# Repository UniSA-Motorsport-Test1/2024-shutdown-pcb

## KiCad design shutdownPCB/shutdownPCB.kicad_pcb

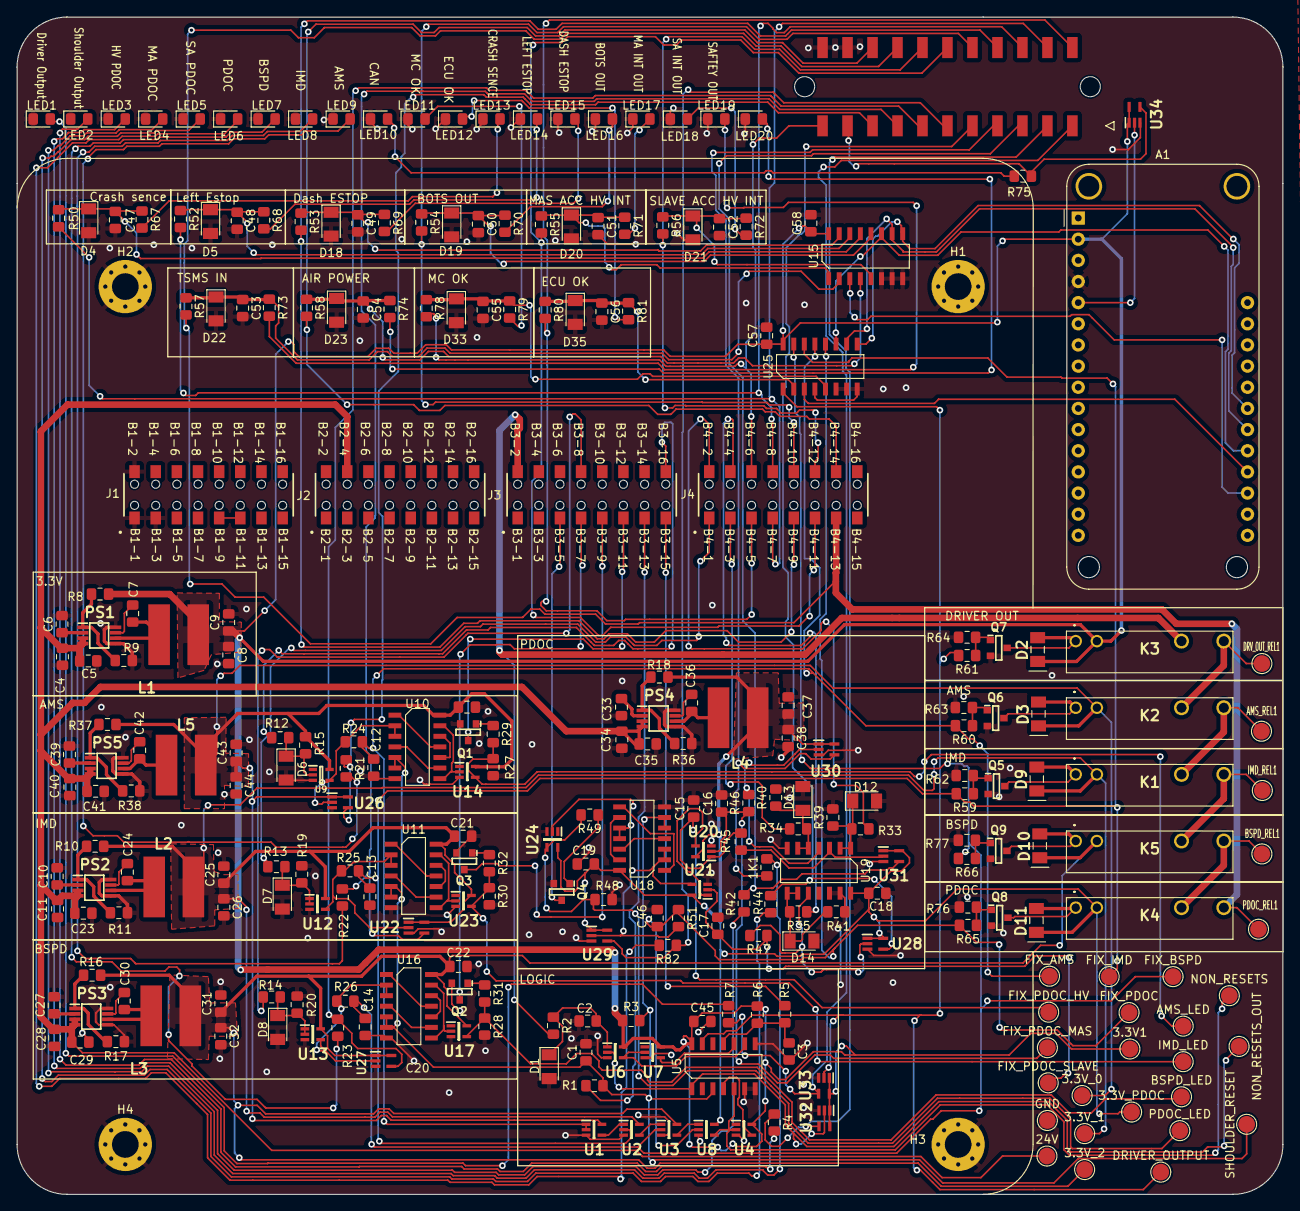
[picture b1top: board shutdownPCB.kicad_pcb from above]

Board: 2 copper layers, 152.0 x 141.4 mm, 277 parts (0 on the bottom side), 168 nets.

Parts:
1K1: CRCW0805; 0805
3.3V1, 3.3V_0, 3.3V_1, 3.3V_2, 3.3V_PDOC, 24V: TestPoint; TestPoint_Pad_D2.0mm
A1: Adafruit_Feather_Generic; Adafruit_Feather_WithMountingHoles
AMS_LED: TestPoint; TestPoint_Pad_D2.0mm
AMS_REL1: TestPoint; TestPoint_Pad_D2.0mm
BSPD_LED: TestPoint; TestPoint_Pad_D2.0mm
BSPD_REL1: TestPoint; TestPoint_Pad_D2.0mm
C1, C2, C3, C12, C13, C14, C15, C16, C17, C46, C47, C48, C49, C50, C51, C52, C53, C54, C55, C56: GCM0805_1u; 0805
C4, C5, C8, C9, C11, C23, C25, C26, C28, C29, C31, C32, C34, C35, C37, C38, C40, C41, C43, C44: 10uF; 0805
C6, C10, C27, C33, C39: 1uF; 0805
C7, C24, C30, C36, C42: 0.1uF; 0805
C18, C19, C20, C21, C22, C45, C57, C58: GCM0805_0.1u; 0805
D1, D4, D5, D6, D7, D8, D12, D13, D14, D18, D19, D20, D21, D22, D23, D33, D35: BZT52HC3V0WF-7; SOD123F
D2, D3, D9, D10, D11: 1N4148W RHG; SOD-123F-2
DRIVER_OUTPUT: TestPoint; TestPoint_Pad_D2.0mm
DRV_OUT_REL1: TestPoint; TestPoint_Pad_D2.0mm
FIX_AMS: TestPoint; TestPoint_Pad_D2.0mm
FIX_BSPD: TestPoint; TestPoint_Pad_D2.0mm
FIX_IMD: TestPoint; TestPoint_Pad_D2.0mm
FIX_PDOC: TestPoint; TestPoint_Pad_D2.0mm
FIX_PDOC_HV: TestPoint; TestPoint_Pad_D2.0mm
FIX_PDOC_MAS: TestPoint; TestPoint_Pad_D2.0mm
FIX_PDOC_SLAVE: TestPoint; TestPoint_Pad_D2.0mm
GND: TestPoint; TestPoint_Pad_D2.0mm
H1, H2, H3, H4: MountingHole_Pad; MountingHole_3.2mm_M3_Pad_Via
IMD_LED: TestPoint; TestPoint_Pad_D2.0mm
IMD_REL1: TestPoint; TestPoint_Pad_D2.0mm
J1, J2, J3, J4: HLE-108-02-L-DV-BE-K-TR; SAMTEC_HLE-108-02-L-DV-BE-K-TR
J5: 43045-2215; MOLEX_43045-22YY_22_PIN
K1, K2, K3, K4, K5: APAN3103
L1, L2, L3, L4, L5: 744062150; 2727
LED1, LED2, LED3, LED4, LED5, LED6, LED7, LED8, LED9, LED10, LED11, LED12: GREEN; 0805
LED13, LED14, LED15, LED16, LED17, LED18, LED19, LED20: BLUE; 0805
NON_RESETS: TestPoint; TestPoint_Pad_D2.0mm
NON_RESETS_OUT: TestPoint; TestPoint_Pad_D2.0mm
PDOC_LED: TestPoint; TestPoint_Pad_D2.0mm
PDOC_REL1: TestPoint; TestPoint_Pad_D2.0mm
PS1, PS2, PS3, PS4, PS5: MCP16311-E_MS; MSOP-8
Q1, Q2, Q3, Q4: SI2318DS-T1-BE3; SOT-23-3
Q5, Q6, Q7, Q8, Q9: BC816-25HVL; SOT-23-3
R1, R2, R3, R4, R5, R6, R7, R8, R9, R10, R11, R15, R16, R17, R18, R19, R20, R21, R22, R23, R24, R25, R26, R27, R28, R29, R30, R31, R32, R36, R37, R38, R39, R40, R41, R42, R44, R45, R46, R47, R48, R49, R51, R59, R60, R61, R62, R63, R64, R65, R66, R67, R68, R69, R70, R71, R72, R73, R74, R75, R76, R77, R79, R81, R82: CRCW0805; 0805
R12, R13, R14, R33, R34, R35, R50, R52, R53, R54, R55, R56, R57, R58, R78, R80: CRCW1210; 0805
SHOULDER_RESET: TestPoint; TestPoint_Pad_D2.0mm
U1, U2, U3, U6, U8, U20, U21: 74LVC1G08GW,125; TSSOP-5
U4, U7, U14, U17, U23, U24: 74AHC1GU04GW,125; TSSOP-5
U5: MC14013BDR2G; SOIC-14
U9: TC7S04FU,LF; SOT-353-5
U10, U11, U16, U18: MC74AC02DR2G; SOIC-14
U12, U13: 74AUP1G32GW,125; TSSOP-5
U15, U25: CD4051BM96G3; SOIC-16
U19: CD4071BM96; SOIC-14
U22, U26, U27, U28, U29, U30, U31, U32, U33, U34: SN74LVC1G126; SC70-5

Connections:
/3.3V: 3.3V1.1, A1.2 (3V3), C8.1, C9.1, C45.1, C57.1, C58.1, D2.1 (K), K3.2, L1.2, R3.1, R6.1, R8.1, U4.5 (VCC), U5.14 (VDD), U6.5 (VCC), U7.5 (VCC), U15.16 (VDD), U25.16 (VDD), U32.1, U32.5, U33.1, U33.5, U34.1, U34.5
/3.3V_0: 3.3V_0.1, C20.1, C43.1, C44.1, D3.1 (K), K2.2, L5.2, R15.1, R37.1, U1.5 (VCC), U9.5 (VCC), U10.14 (VDD), U14.5 (VCC), U26.1, U26.5
/3.3V_1: 3.3V_1.1, C21.1, C25.1, C26.1, D9.1 (K), K1.2, L2.2, R10.1, U2.5 (VCC), U11.14 (VDD), U12.5 (Vcc), U22.1, U22.5, U23.5 (VCC)
/3.3V_2: 3.3V_2.1, C22.1, C31.1, C32.1, D10.1 (K), K5.2, L3.2, R16.1, U3.5 (VCC), U13.5 (Vcc), U16.14 (VDD), U17.5 (VCC), U27.1, U27.5
/3.3V_PDOC: 3.3V_PDOC.1, C18.1, C19.1, C37.1, C38.1, D11.1 (K), K4.2, L4.2, R18.1, U8.5 (VCC), U18.14 (VDD), U19.14 (VDD), U20.5 (VCC), U21.5 (VCC), U24.5 (VCC), U28.1, U28.5, U29.1, U29.5, U30.1, U30.5, U31.1, U31.5
/AIR_OUTPUT/DRIVER_OUTPUT: DRIVER_OUTPUT.1, R61.2, U5.13 (Q), U25.1 (X4), U33.2
/Fix_AMS: C12.1, FIX_AMS.1, R24.1, R60.2, U1.1, U1.2, U25.13 (X0)
/Fix_BSPD: C14.1, FIX_BSPD.1, R26.1, R66.2, U3.2, U25.15 (X2)
/Fix_IMD: C13.1, FIX_IMD.1, R25.1, R59.2, U2.2, U25.14 (X1)
/Fix_PDOC: C46.2, FIX_PDOC.1, R51.1, R65.2, U8.2, U25.12 (X3)
/NonDriverResetableInputs/AMS_LED: J5.9, R21.1, U26.4
/NonDriverResetableInputs/BSPD_LED: J5.7, R23.1, U27.4
/NonDriverResetableInputs/HV_IMD_LED: J5.8, R22.1, U22.4
/NonDriverResetableInputs/HV_PDOC_LED: J5.3, R42.1, U31.4
/NonDriverResetableInputs/MA_PDOC_LED: 1K1.1, J5.4, U30.4
/NonDriverResetableInputs/PDOC_LED: J5.6, R82.1, U29.4
/NonDriverResetableInputs/SA_PDOC_LED: J5.5, R44.1, U28.4
/NonDriverResetableInputs/SHOULDER_RESET_SIGNAL: C1.1, R1.1, R3.2, SHOULDER_RESET.1, U5.3 (C), U10.5, U10.6, U11.5, U11.6, U16.5, U16.6, U18.5, U18.6
/connector/AIR_POWER: J4.14, J5.20, R58.2
/connector/BOTS_OUT: J4.10, J5.16, R54.2
/connector/BSPD_TRIGGER: J3.8, R14.2
/connector/CRASH_SENSOR_MONITOR: J4.7, J5.13, R50.2
/connector/DASH_AMS_LED: J3.11, Q1.3 (D)
/connector/DASH_BSPD_LED: J3.7, Q2.3 (D)
/connector/DASH_ESTOP_OUT: J4.9, J5.15, R53.2
/connector/DASH_IMD_LED: J3.9, Q3.3 (D)
/connector/DASH_PDOC_LED: J3.5, Q4.3 (D)
/connector/DISCHARGE_ENABLE_SIGNAL: J3.16, R12.2
/connector/DRIVER_OUTPUT_LED: J5.1, R7.1, U33.4
/connector/DRIVER_RESET_IN: J3.15, R5.2
/connector/ECU_OK: J4.5, J5.12, R80.2
/connector/FEATHER_OUT: J5.10, R75.1, U34.4
/connector/HV_BOX_IMD_OK: J4.1, R13.2
/connector/HV_BOX_PDOC_OK: J4.2, R33.2
/connector/LEFT_ESTOP_OUT: J4.8, J5.14, R52.2
/connector/MASTER_ACC_HV_INT_OUT: J4.11, J5.17, R55.2
/connector/MASTER_ACC_PDOC_OK: J4.3, R34.2
/connector/MC_OK_INDICATOR: J4.6, J5.11, R78.2
/connector/RADIATOR_WATER_PUMP_24V: J1.9, J1.11
/connector/SAFETY_24V: 24V.1, C4.1, C5.1, C11.1, C23.1, C28.1, C29.1, C34.1, C35.1, C40.1, C41.1, J2.4, PS1.3 (EN), PS1.4 (VIN), PS2.3 (EN), PS2.4 (VIN), PS3.3 (EN), PS3.4 (VIN), PS4.3 (EN), PS4.4 (VIN), PS5.3 (EN), PS5.4 (VIN)
/connector/SAFTEY_IN: J3.2, K3.3, R2.2
/connector/SAFTEY_OUT: J4.13, J5.19, K4.4, PDOC_REL1.1, R57.2
/connector/SHOULDER_OUT_LED: J5.2, R4.1, U32.4
/connector/SHOULDER_RESET: J3.13, R1.2
/connector/SLAVE_ACC_HV_INT_OUT: J4.12, J5.18, R56.2
/connector/SLAVE_ACC_PDOC_OK: J4.4, R35.2
/feather/ECU_OK_SIGNAL: C56.1, D35.1 (K), R80.1, R81.1, U25.2 (X6)
/feather/MC_OK_SIGNAL: C55.1, D33.1 (K), R78.1, R79.1, U25.5 (X5)
/feather/MUX_A: A1.21 (D2), U15.11 (A), U25.11 (A)
/feather/MUX_AIR_PATH: A1.19 (D0), U15.3 (X)
/feather/MUX_B: A1.22 (D3), U15.10 (B), U25.10 (B)
/feather/MUX_C: A1.23 (D4), U15.9 (C), U25.9 (C)
/feather/MUX_Fixed_Inputs: A1.20 (D1), U25.3 (X)
GND: A1.4 (GND), C1.2, C2.2, C3.2, C4.2, C5.2, C6.2, C8.2, C9.2, C10.2, C11.2, C12.2, C13.2, C14.2, C15.2, C16.2, C17.2, C18.2, C19.2, C20.2, C21.2, C22.2, C23.2, C25.2, C26.2, C27.2, C28.2, C29.2, C31.2, C32.2, C33.2, C34.2, C35.2, C37.2, C38.2, C39.2, C40.2, C41.2, C43.2, C44.2, C45.2, C46.1, C47.2, C48.2, C49.2, C50.2, C51.2, C52.2, C53.2, C54.2, C55.2, C56.2, C57.2, C58.2, D1.2 (A), D4.2 (A), D5.2 (A), D6.2 (A), D7.2 (A), D8.2 (A), D12.2 (A), D13.2 (A), D14.2 (A), D18.2 (A), D19.2 (A), D20.2 (A), D21.2 (A), D22.2 (A), D23.2 (A), D33.2 (A), D35.2 (A), GND.1, H1.1, H2.1, H3.1, H4.1, J1.1, J1.2, J1.3, J5.21, J5.22, LED1.1 (K), LED2.1 (K), LED3.1 (K), LED4.1 (K), LED5.1 (K), LED6.1 (K), LED7.1 (K), LED8.1 (K), LED9.1 (K), LED10.1 (K), LED11.1 (K), LED12.1 (K), LED13.1 (K), LED14.1 (K), LED15.1 (K), LED16.1 (K), LED17.1 (K), LED18.1 (K), LED19.1 (K), LED20.1 (K), PS1.5 (P_GND), PS1.8 (A_GND), PS2.5 (P_GND), PS2.8 (A_GND), PS3.5 (P_GND), PS3.8 (A_GND), PS4.5 (P_GND), PS4.8 (A_GND), PS5.5 (P_GND), PS5.8 (A_GND), Q1.2 (S), Q2.2 (S), Q3.2 (S), Q4.2 (S), Q5.2, Q6.2, Q7.2, Q8.2, Q9.2, R9.2, R11.2, R17.2, R19.2, R20.2, R27.2, R28.2, R30.2, R36.2, R38.2, R39.2, R40.2, R41.2, R48.2, R62.2, R63.2, R64.2, R76.2, R77.2, U1.3 (GND), U2.3 (GND), U3.3 (GND), U4.3 (GND), U5.6 (S), U5.7 (VSS), U5.8 (S), U6.3 (GND), U7.3 (GND), U8.3 (GND), U9.3 (GND), U10.7 (VSS), U11.7 (VSS), U12.3 (GND), U13.3 (GND), U14.3 (GND), U15.6 (Inh), U15.7 (VEE), U15.8 (VSS), U16.7 (VSS), U17.3 (GND), U18.7 (VSS), U19.7 (VSS), U19.12, U19.13, U20.3 (GND), U21.3 (GND), U22.3, U23.3 (GND), U24.3 (GND), U25.4 (X7), U25.6 (Inh), U25.7 (VEE), U25.8 (VSS), U26.3, U27.3, U28.3, U29.3, U30.3, U31.3, U32.3, U33.3, U34.3
unnamed: A1.5 (A0), U34.2
unnamed: AMS_LED.1, R27.1, R29.2, U14.4
unnamed: AMS_REL1.1, K1.3, K2.4
unnamed: BSPD_LED.1, R28.1, R31.2, U17.4
unnamed: BSPD_REL1.1, K4.3, K5.4
unnamed: C15.1, FIX_PDOC_HV.1, R45.1, U20.1
unnamed: C16.1, FIX_PDOC_MAS.1, R46.1, U20.2
unnamed: C17.1, FIX_PDOC_SLAVE.1, R47.1, U21.2
unnamed: C2.1, D1.1 (K), R2.1, U6.1
unnamed: D2.2 (A), K3.1, Q7.3
unnamed: D3.2 (A), K2.1, Q6.3
unnamed: C47.1, D4.1 (K), R50.1, R67.1, U15.13 (X0)
unnamed: C48.1, D5.1 (K), R52.1, R68.1, U15.14 (X1)
unnamed: D6.1 (K), R12.1, R15.2, U9.2
unnamed: D7.1 (K), R13.1, R19.1, U12.1, U12.2
unnamed: D8.1 (K), R14.1, R20.1, U13.1, U13.2
unnamed: D9.2 (A), K1.1, Q5.3
unnamed: D10.2 (A), K5.1, Q9.3
unnamed: D11.2 (A), K4.1, Q8.3
unnamed: D12.1 (K), R33.1, R39.1, U19.1, U19.2
unnamed: D13.1 (K), R34.1, R40.1, U19.5, U19.6
unnamed: D14.1 (K), R35.1, R41.1, U19.8, U19.9
unnamed: C49.1, D18.1 (K), R53.1, R69.1, U15.15 (X2)
unnamed: C50.1, D19.1 (K), R54.1, R70.1, U15.12 (X3)
unnamed: C51.1, D20.1 (K), R55.1, R71.1, U15.1 (X4)
unnamed: C52.1, D21.1 (K), R56.1, R72.1, U15.5 (X5)
unnamed: C53.1, D22.1 (K), R57.1, R73.1, U15.2 (X6)
unnamed: C54.1, D23.1 (K), R58.1, R74.1, U15.4 (X7)
unnamed: DRV_OUT_REL1.1, K2.3, K3.4
unnamed: IMD_LED.1, R30.1, R32.2, U23.4
unnamed: IMD_REL1.1, K1.4, K5.3
unnamed: LED1.2 (A), R7.2
unnamed: LED2.2 (A), R4.2
unnamed: LED3.2 (A), R42.2
unnamed: 1K1.2, LED4.2 (A)
unnamed: LED5.2 (A), R44.2
unnamed: LED6.2 (A), R82.2
unnamed: LED7.2 (A), R23.2
unnamed: LED8.2 (A), R22.2
unnamed: LED9.2 (A), R21.2
unnamed: LED10.2 (A), R75.2
unnamed: LED11.2 (A), R79.2
unnamed: LED12.2 (A), R81.2
unnamed: LED13.2 (A), R67.2
unnamed: LED14.2 (A), R68.2
unnamed: LED15.2 (A), R69.2
unnamed: LED16.2 (A), R70.2
unnamed: LED17.2 (A), R71.2
unnamed: LED18.2 (A), R72.2
unnamed: LED19.2 (A), R73.2
unnamed: LED20.2 (A), R74.2
unnamed: PDOC_LED.1, R48.1, R49.2, U24.4
unnamed: C7.1, PS1.7 (BOOST)
unnamed: C7.2, L1.1, PS1.6 (SW)
unnamed: C6.1, PS1.2 (VCC)
unnamed: PS1.1 (VFB), R8.2, R9.1
unnamed: C24.1, PS2.7 (BOOST)
unnamed: C24.2, L2.1, PS2.6 (SW)
unnamed: C10.1, PS2.2 (VCC)
unnamed: PS2.1 (VFB), R10.2, R11.1
unnamed: C30.1, PS3.7 (BOOST)
unnamed: C30.2, L3.1, PS3.6 (SW)
unnamed: C27.1, PS3.2 (VCC)
unnamed: PS3.1 (VFB), R16.2, R17.1
unnamed: C36.1, PS4.7 (BOOST)
unnamed: C36.2, L4.1, PS4.6 (SW)
unnamed: C33.1, PS4.2 (VCC)
unnamed: PS4.1 (VFB), R18.2, R36.1
unnamed: C42.1, PS5.7 (BOOST)
unnamed: C42.2, L5.1, PS5.6 (SW)
unnamed: C39.1, PS5.2 (VCC)
unnamed: PS5.1 (VFB), R37.2, R38.1
unnamed: Q1.1 (G), R29.1
unnamed: Q2.1 (G), R31.1
unnamed: Q3.1 (G), R32.1
unnamed: Q4.1 (G), R49.1
unnamed: Q5.1, R59.1, R62.1
unnamed: Q6.1, R60.1, R63.1
unnamed: Q7.1, R61.1, R64.1
unnamed: Q8.1, R65.1, R76.1
unnamed: Q9.1, R66.1, R77.1
unnamed: R24.2, U9.4, U10.2, U10.3, U26.2
unnamed: R25.2, U11.2, U11.3, U12.4, U22.2
unnamed: R26.2, U13.4, U16.2, U16.3, U27.2
unnamed: R45.2, U19.3, U31.2
unnamed: R46.2, U19.4, U30.2
unnamed: R47.2, U19.10, U28.2
unnamed: R51.2, U18.2, U18.3, U21.4, U29.2
unnamed: U1.4, U2.1
unnamed: U2.4, U3.1
unnamed: U3.4, U8.1
unnamed: NON_RESETS.1, U4.2, U5.5 (D), U8.4
unnamed: NON_RESETS_OUT.1, U5.1 (Q), U6.2, U32.2
unnamed: U4.4, U5.4 (R)
unnamed: C3.1, R5.1, R6.2, U5.11 (C)
unnamed: U5.9 (D), U6.4, U7.2
unnamed: U5.10 (R), U7.4
unnamed: U10.1, U10.11
unnamed: U10.4, U10.9
unnamed: U10.10, U10.12
unnamed: U10.8, U10.13, U14.2
unnamed: U11.1, U11.11
unnamed: U11.4, U11.9
unnamed: U11.10, U11.12
unnamed: U11.8, U11.13, U23.2
unnamed: U16.1, U16.11
unnamed: U16.4, U16.9
unnamed: U16.10, U16.12
unnamed: U16.8, U16.13, U17.2
unnamed: U18.1, U18.8
unnamed: U18.10, U18.11, U24.2
unnamed: U18.4, U18.12
unnamed: U18.9, U18.13
unnamed: U20.4, U21.1

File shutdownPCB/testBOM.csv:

Reference,Value,Datasheet,Footprint,Qty,DNP
"1K1,R1,R2,R3,R4,R5,R6,R7,R8,R9,R10,R11,R15,R16,R17,R18,R19,R20,R21,R22,R23,R24,R25,R26,R27,R28,R29,R30,R31,R32,R36,R37,R38,R39,R40,R41,R42,R44,R45,R46,R47,R48,R49,R51,R59,R60,R61,R62,R63,R64,R65,R66,R67,R68,R69,R70,R71,R72,R73,R74,R75,R76,R77,R79,R81,R82",CRCW0805,https://au.mouser.com/datasheet/2/427/dcrcwe3-1762152.pdf,UniSA_Motorsport_Resistor:0805,66,
"3.3V1,3.3V_0,3.3V_1,3.3V_2,3.3V_PDOC1,24V1,AMS_LED1,AMS_REL1,BSPD_LED1,BSPD_REL1,DRIVER_OUTPUT1,DRV_OUT_REL1,FIX_AMS1,FIX_BSPD1,FIX_IMD1,FIX_PDOC1,FIX_PDOC_HV1,FIX_PDOC_MAS1,FIX_PDOC_SLAVE1,GND1,IMD_LED1,IMD_REL1,NON_RESETS1,NON_RESETS_OUT1,PDOC_LED1,PDOC_REL1,SHOULDER_RESET1",TestPoint,~,TestPoint:TestPoint_Pad_D2.0mm,27,
A1,Adafruit_Feather_Generic,https://cdn-learn.adafruit.com/downloads/pdf/adafruit-feather.pdf,Module:Adafruit_Feather_WithMountingHoles,1,
"C1,C2,C3,C12,C13,C14,C15,C16,C17,C46,C47,C48,C49,C50,C51,C52,C53,C54,C55,C56",GCM0805_1u,https://au.mouser.com/datasheet/2/281/murata_03122018_GCM_Se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,UniSA_Motorsport_Capacitor:0805,20,
"C4,C5,C8,C9,C11,C23,C25,C26,C28,C29,C31,C32,C34,C35,C37,C38,C40,C41,C43,C44",10uF,~,UniSA_Motorsport_Resistor:0805,20,
"C6,C10,C27,C33,C39",1uF,~,UniSA_Motorsport_Resistor:0805,5,
"C7,C24,C30,C36,C42",0.1uF,~,UniSA_Motorsport_Resistor:0805,5,
"C18,C19,C20,C21,C22,C45,C57,C58",GCM0805_0.1u,https://au.mouser.com/datasheet/2/281/murata_03122018_GCM_Se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,UniSA_Motorsport_Capacitor:0805,8,
"D1,D4,D5,D6,D7,D8,D12,D13,D14,D18,D19,D20,D21,D22,D23,D33,D35",BZT52HC3V0WF-7,https://au.mouser.com/datasheet/2/115/BZT52HC2V4WF_-_BZT52HC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,UniSA_Motorsport_SO:SOD123F,17,
"D2,D3,D9,D10,D11",1N4148W RHG,https://au.mouser.com/ProductDetail/Taiwan-Semiconductor/1N4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,UniSA_Motorsport_Diode:SOD-123F-2,5,
"H1,H2,H3,H4",MountingHole_Pad,~,MountingHole:MountingHole_3.2mm_M3_Pad_Via,4,
"J1,J2,J3,J4",HLE-108-02-L-DV-BE-K-TR,https://au.mouser.com/ProductDetail/Samtec/HLE-108-02-L-DV-B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,UniSA_Motorsport_Connector:SAMTEC_HLE-108-02-L-DV-BE-K-TR,4,
J5,43045-2215,https://au.mouser.com/ProductDetail/Molex/43045-2215?qs=%2Fy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,UniSA_Motorsport_Connector:MOLEX_43045-22YY_22_PIN,1,
"K1,K2,K3,K4,K5",APAN3103,https://octopart.com/apan3103-panasonic-73741787?r=sp,UniSA_Motorsport_Others:APAN3103,5,
"L1,L2,L3,L4,L5",744062150,https://componentsearchengine.com/Datasheets/1/744062150.pdf,UniSA_Motorsport_Resistor:2727,5,
"LED1,LED2,LED3,LED4,LED5,LED6,LED7,LED8,LED9,LED10,LED11,LED12",GREEN,https://au.mouser.com/datasheet/2/109/Dialight_CBI_data_599-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,UniSA_Motorsport_Diode:0805,12,
"LED13,LED14,LED15,LED16,LED17,LED18,LED19,LED20",BLUE,https://au.mouser.com/datasheet/2/109/Dialight_CBI_data_599-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,UniSA_Motorsport_Diode:0805,8,
"PS1,PS2,PS3,PS4,PS5",MCP16311-E_MS,-- mixed values --,UniSA_Motorsport_SO:MSOP-8,5,
"Q1,Q2,Q3,Q4",SI2318DS-T1-BE3,https://au.mouser.com/ProductDetail/Vishay-Siliconix/SI2318D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,UniSA_Motorsport_SOT_TO:SOT-23-3,4,
"Q5,Q6,Q7,Q8,Q9",BC816-25HVL,https://au.mouser.com/datasheet/2/916/BC816H_SER-1839928.pdf,UniSA_Motorsport_SOT_TO:SOT-23-3,5,
"R12,R13,R14,R33,R34,R35,R50,R52,R53,R54,R55,R56,R57,R58,R78,R80",CRCW1210,https://au.mouser.com/datasheet/2/427/dcrcwe3-1762152.pdf,UniSA_Motorsport_Resistor:0805,16,
"U1,U2,U3,U6,U8,U20,U21","74LVC1G08GW,125",https://au.mouser.com/datasheet/2/916/74LVC1G08-2937782.pdf,UniSA_Motorsport_SO:TSSOP-5,7,
"U4,U7,U14,U17,U23,U24","74AHC1GU04GW,125",https://au.mouser.com/datasheet/2/916/74AHC1GU04-2937201.pdf,UniSA_Motorsport_SO:TSSOP-5,6,
U5,MC14013BDR2G,https://au.mouser.com/ProductDetail/onsemi/MC14013BDR2G?qs=g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,UniSA_Motorsport_SO:SOIC-14,1,
U9,"TC7S04FU,LF",https://au.mouser.com/ProductDetail/Toshiba/TC7S04FULF?qs=sG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,UniSA_Motorsport_SOT_TO:SOT-353-5,1,
"U10,U11,U16,U18",MC74AC02DR2G,https://au.mouser.com/datasheet/2/308/1/MC74AC02_D-2315605.pdf,UniSA_Motorsport_SO:SOIC-14,4,
"U12,U13","74AUP1G32GW,125",https://au.mouser.com/datasheet/2/916/74AUP1G32-1511907.pdf,UniSA_Motorsport_SO:TSSOP-5,2,
"U15,U25",CD4051BM96G3,http://www.ti.com/lit/ds/symlink/cd4051b.pdf?ts=1588338734665,UniSA_Motorsport_SO:SOIC-16,2,
U19,CD4071BM96,https://au.mouser.com/ProductDetail/Texas-Instruments/CD4071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,UniSA_Motorsport_SO:SOIC-14,1,
"U22,U26,U27,U28,U29,U30,U31,U32,U33,U34",SN74LVC1G126 ,https://au.mouser.com/ProductDetail/Texas-Instruments/SN74LV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,UniSA_Motorsport_SO:SC70-5,10,

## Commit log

2024-04-23 before design review
2024-09-12 Updated 12 Sep
2025-01-11 My last update
